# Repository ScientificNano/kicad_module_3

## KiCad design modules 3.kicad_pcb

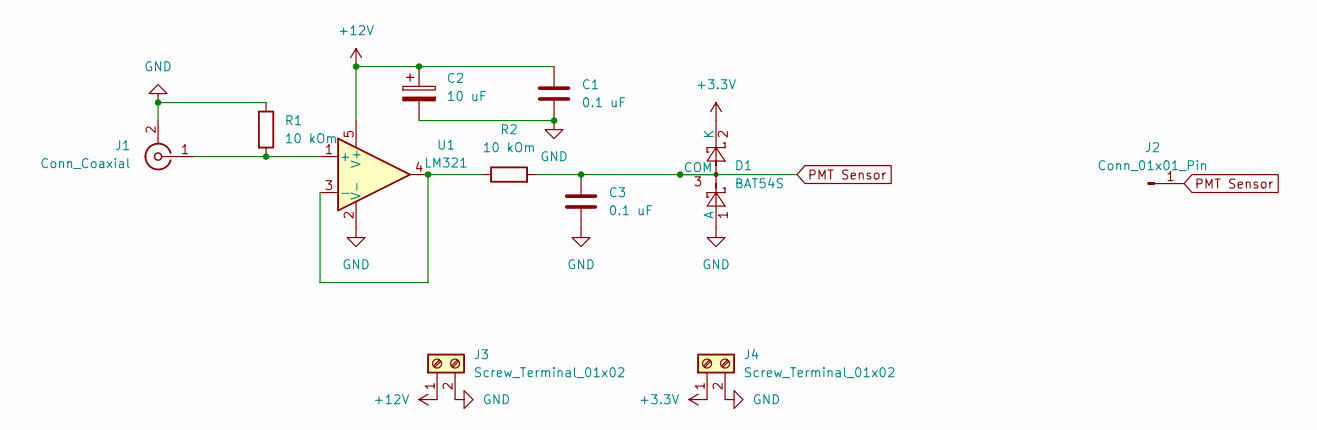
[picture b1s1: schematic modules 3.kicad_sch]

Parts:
C1, C3: 0.1 uF; C_0805_2012Metric_Pad1.18x1.45mm_HandSolder
C2: 10 uF; CP_EIA-3528-21_Kemet-B_Pad1.50x2.35mm_HandSolder
D1: BAT54S; SOT-23
J1: Conn_Coaxial; BNC_Amphenol_031-5539_Vertical
J2: Conn_01x01_Pin; PinHeader_1x01_P2.54mm_Vertical
J3, J4: Screw_Terminal_01x02; TerminalBlock_bornier-2_P5.08mm
R1, R2: 10 kOm; R_0805_2012Metric_Pad1.20x1.40mm_HandSolder
U1: LM321; SOT-23-5

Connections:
+3.3V: D1.2 (K), J4.1
+12V: C1.1, C2.1, J3.1, U1.5 (V+)
GND: C1.2, C2.2, C3.2, D1.1 (A), J1.2 (Ext), J3.2, J4.2, R1.1, U1.2 (V-)
unnamed: J1.1 (In), R1.2, U1.1 (+)
unnamed: R2.1, U1.3 (-), U1.4
PMT Sensor: C3.1, D1.3 (COM), J2.1, R2.2

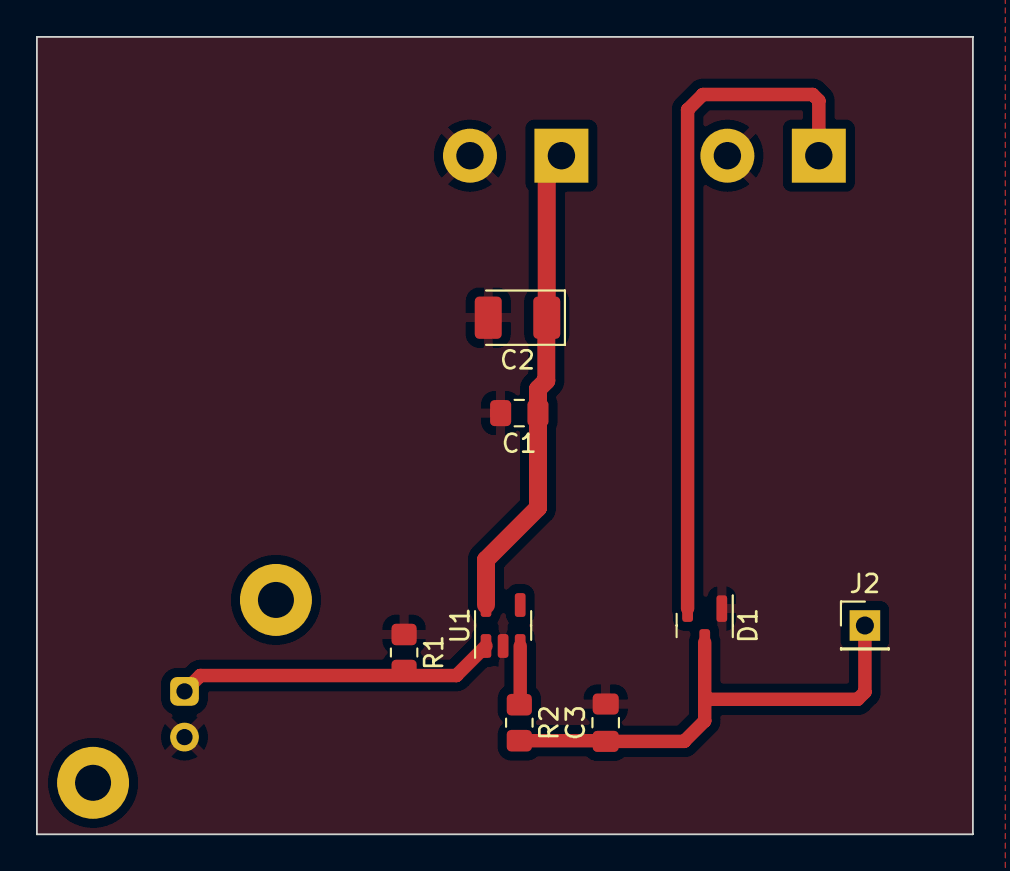
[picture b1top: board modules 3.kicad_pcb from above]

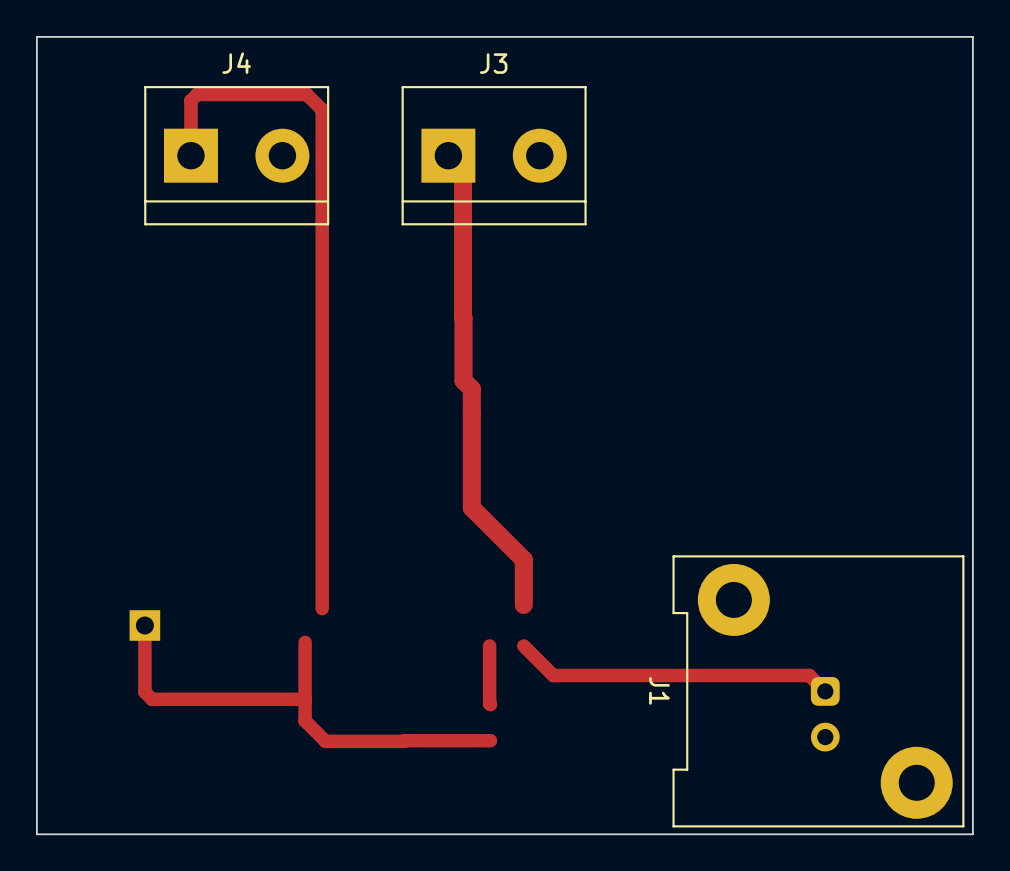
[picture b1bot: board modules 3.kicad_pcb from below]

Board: 2 copper layers, 52.0 x 44.3 mm, 11 parts (3 on the bottom side), 6 nets.

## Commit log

2023-08-11 Add new module 3
